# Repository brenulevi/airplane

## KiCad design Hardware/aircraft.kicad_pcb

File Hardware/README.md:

# FCU
- UART1: Comm with NU
- UART2: Logging Debug
- UART3: Extra UART (Radio Control)
- UART4: Extra UART (Camera)

- I2C1: Comm with NU
- I2C2: Peripherals (PWM Driver, EEPROM)

- TIM3: Actuators (CH1 Ailerons, CH2 Elevator, CH3 Rudder, CH4 Flaps)
- TIM1: Propulsions (CH1 ESC1, CH3 ESC3)

- SPI1: Peripherals (Flash)

- SWD: Coding/Debug

- SDIO: SD Card (1bit)

- GPIOA, GPIOC, GPIOE: Comm with NU (Output)
- GPIOB, GPIOD, GPIOF: Comm with NU (Input)

- DFU_USB_DP
- DFU_USB_DM
- DFU_USB_VBUS

# NU
- UART1: Comm with FCU
- UART2: Logging Debug
- UART3: Peripheral (GNSS)
- UART4: Extra UART

- I2C1: Comm with FCU
- I2C2: Peripherals (Temperature, Baro, EEPROM, MAG)
- I2C3: Extra I2C (Pitot Sensor)

- SPI1: Peripherals (Flash) + 1 GPIO CS
- SPI2: Peripherals (IMU) + 1 GPIO CS

- SWD: Coding/Debug

- GPIO_GPS_PSS
- GPIO_GPS_LNA_EN
- GPIO_GPS_NRST

- GPIOA, GPIOC, GPIOE: Comm with NU (Input)
- GPIOB, GPIOD, GPIOF: Comm with NU (Output)

- DFU_USB_DP
- DFU_USB_DM

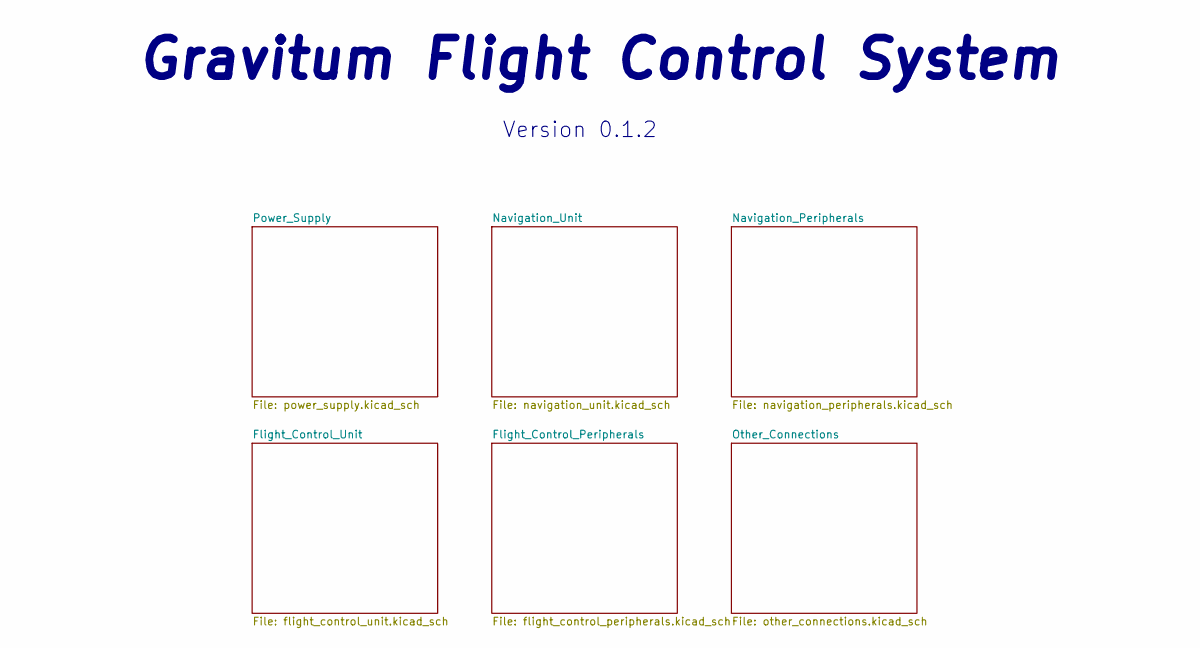
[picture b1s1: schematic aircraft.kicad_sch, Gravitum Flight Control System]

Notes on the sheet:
Gravitum Flight Control System
Version 0.1.2

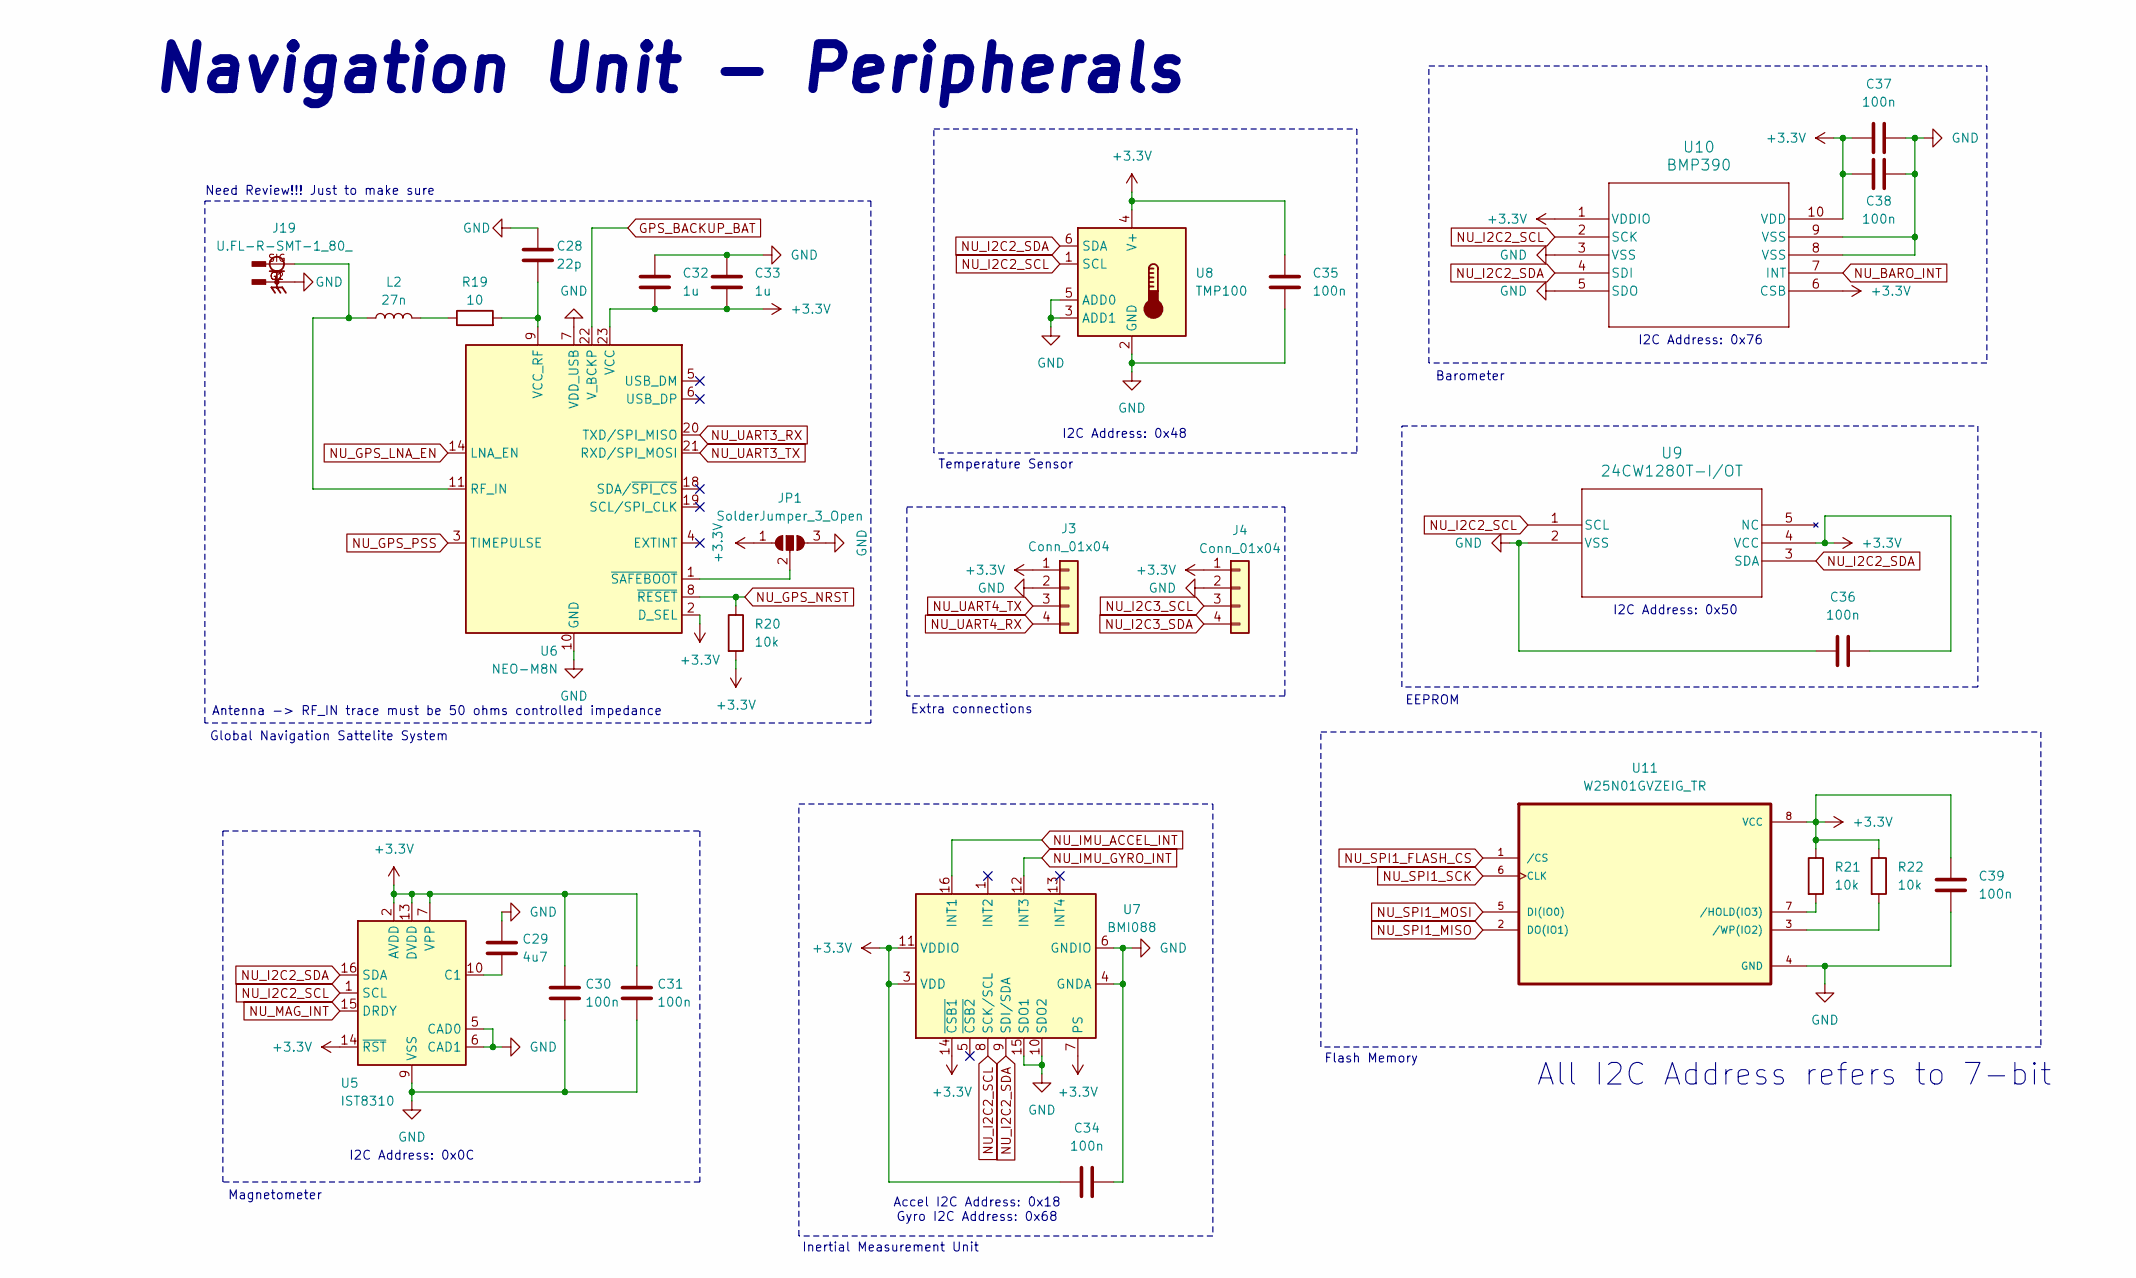
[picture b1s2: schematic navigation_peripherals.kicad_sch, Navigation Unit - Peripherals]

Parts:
C28: 22p; C_0603_1608Metric; MPN C0603C220J8GACTU
C29: 4u7; C_0805_2012Metric_Pad1.18x1.45mm_HandSolder; MPN CL21B475KPFNNNE
C30, C31, C34, C35, C36, C37, C38, C39: 100n; C_0603_1608Metric; MPN C0603C104K8RACTU
C32, C33: 1u; C_0603_1608Metric_Pad1.08x0.95mm_HandSolder; MPN CL10B105KP8NNNC
J3, J4: Conn_01x04; JST_PH_S4B-PH-K_1x04_P2.00mm_Horizontal; MPN S4B-PH-K-S
J19: U.FL-R-SMT-1_80_; HIROSE_U.FL-R-SMT-1_80_; PARTREV Jul.1.2022
JP1: SolderJumper_3_Open; SolderJumper-3_P1.3mm_Open_RoundedPad1.0x1.5mm_NumberLabels
L2: 27n; L_0603_1608Metric_Pad1.05x0.95mm_HandSolder; MPN B82496C3270J000
R19: 10; R_0603_1608Metric_Pad0.98x0.95mm_HandSolder; MPN RMCF0603FT10R0
R20, R21, R22: 10k; R_0603_1608Metric_Pad0.98x0.95mm_HandSolder; MPN RC0603FR-0710KL
U5: IST8310; LGA-16_3x3mm_P0.5mm; MPN IST8310
U6: NEO-M8N; XCVR_NEO-M8N-0; MPN NEO-M8N-0
U7: BMI088; Bosch_LGA-16_4.5x3mm_P0.5mm_LayoutBorder7x1y_ClockwisePinNu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; MPN BMI088
U8: TMP100; SOT-23-6; MPN TMP100NA-3K
U9: 24CW1280T-I/OT; SOT-23-5_2P9X1P6_MCH; MPN 24CW1280T-I/OT
U10: BMP390; 10LGA_2X2X0p75_BOS; MPN BMP390
U11: W25N01GVZEIG_TR; SON127P800X600X80-9N; MPN W25N01GVZEIG-TR

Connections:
+3.3V: C30.1, C31.1, C32.2, C33.2, C34.1, C35.2, C36.1, C37.2, C38.2, C39.1, J3.1, J4.1, JP1.1 (A), R20.2, R21.1, R22.1, U5.2 (AVDD), U5.7 (VPP), U5.13 (DVDD), U5.14 (~RST), U6.2 (D_SEL), U6.23 (VCC), U7.3 (VDD), U7.7 (PS), U7.11 (VDDIO), U7.14 (~CSB1), U8.4 (V+), U9.4 (VCC), U10.1 (VDDIO), U10.6 (CSB), U10.10 (VDD), U11.8 (VCC); also elsewhere on the board
GND: C28.1, C29.1, C30.2, C31.2, C32.1, C33.1, C34.2, C35.1, C36.2, C37.1, C38.1, C39.2, J3.2, J4.2, J19.G1, J19.G2, JP1.3 (B), U5.5 (CAD0), U5.6 (CAD1), U5.9 (VSS), U5.11 (VSS), U6.7 (VDD_USB), U6.10 (GND), U6.12 (GND), U6.13 (GND), U6.24 (GND), U7.2 (GNDA), U7.4 (GNDA), U7.6 (GNDIO), U7.10 (SDO2), U7.15 (SDO1), U8.2 (GND), U8.3 (ADD1), U8.5 (ADD0), U9.2 (VSS), U10.3 (VSS), U10.5 (SDO), U10.8 (VSS), U10.9 (VSS), U11.4 (GND); also elsewhere on the board
GPS_BACKUP_BAT: U6.22 (V_BCKP); also elsewhere on the board
NU_BARO_INT: U10.7 (INT); also elsewhere on the board
NU_GPS_LNA_EN: U6.14 (LNA_EN); also elsewhere on the board
NU_GPS_NRST: R20.1, U6.8 (~RESET); also elsewhere on the board
NU_GPS_PSS: U6.3 (TIMEPULSE); also elsewhere on the board
NU_I2C2_SCL: U5.1 (SCL), U7.8 (SCK/SCL), U8.1 (SCL), U9.1 (SCL), U10.2 (SCK); also elsewhere on the board
NU_I2C2_SDA: U5.16 (SDA), U7.9 (SDI/SDA), U8.6 (SDA), U9.3 (SDA), U10.4 (SDI); also elsewhere on the board
NU_I2C3_SCL: J4.3; also elsewhere on the board
NU_I2C3_SDA: J4.4; also elsewhere on the board
NU_IMU_ACCEL_INT: U7.16 (INT1); also elsewhere on the board
NU_IMU_GYRO_INT: U7.12 (INT3); also elsewhere on the board
NU_MAG_INT: U5.15 (DRDY); also elsewhere on the board
NU_SPI1_FLASH_CS: U11.1 (/CS); also elsewhere on the board
NU_SPI1_MISO: U11.2 (DO(IO1)); also elsewhere on the board
NU_SPI1_MOSI: U11.5 (DI(IO0)); also elsewhere on the board
NU_SPI1_SCK: U11.6 (CLK); also elsewhere on the board
NU_UART3_RX: U6.20 (TXD/SPI_MISO); also elsewhere on the board
NU_UART3_TX: U6.21 (RXD/SPI_MOSI); also elsewhere on the board
NU_UART4_RX: J3.4; also elsewhere on the board
NU_UART4_TX: J3.3; also elsewhere on the board
unnamed: JP1.2 (C), U6.1 (~SAFEBOOT)
unnamed: L2.2, R19.1
unnamed: C29.2, U5.10 (C1)
unnamed: J19.SIG, L2.1, U6.11 (RF_IN)
unnamed: C28.2, R19.2, U6.9 (VCC_RF)
unnamed: R21.2, U11.7 (/HOLD(IO3))
unnamed: R22.2, U11.3 (/WP(IO2))

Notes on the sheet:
Magnetometer
Navigation Unit - Peripherals
I2C Address: 0x48
Flash Memory
I2C Address: 0x76
Barometer
Temperature Sensor
Accel I2C Address: 0x18 Gyro I2C Address: 0x68
EEPROM
Need Review!!! Just to make sure
Global Navigation Sattelite System
Inertial Measurement Unit
All I2C Address refers to 7-bit
Antenna -> RF_IN trace must be 50 ohms controlled impedance
I2C Address: 0x0C
I2C Address: 0x50
Extra connections

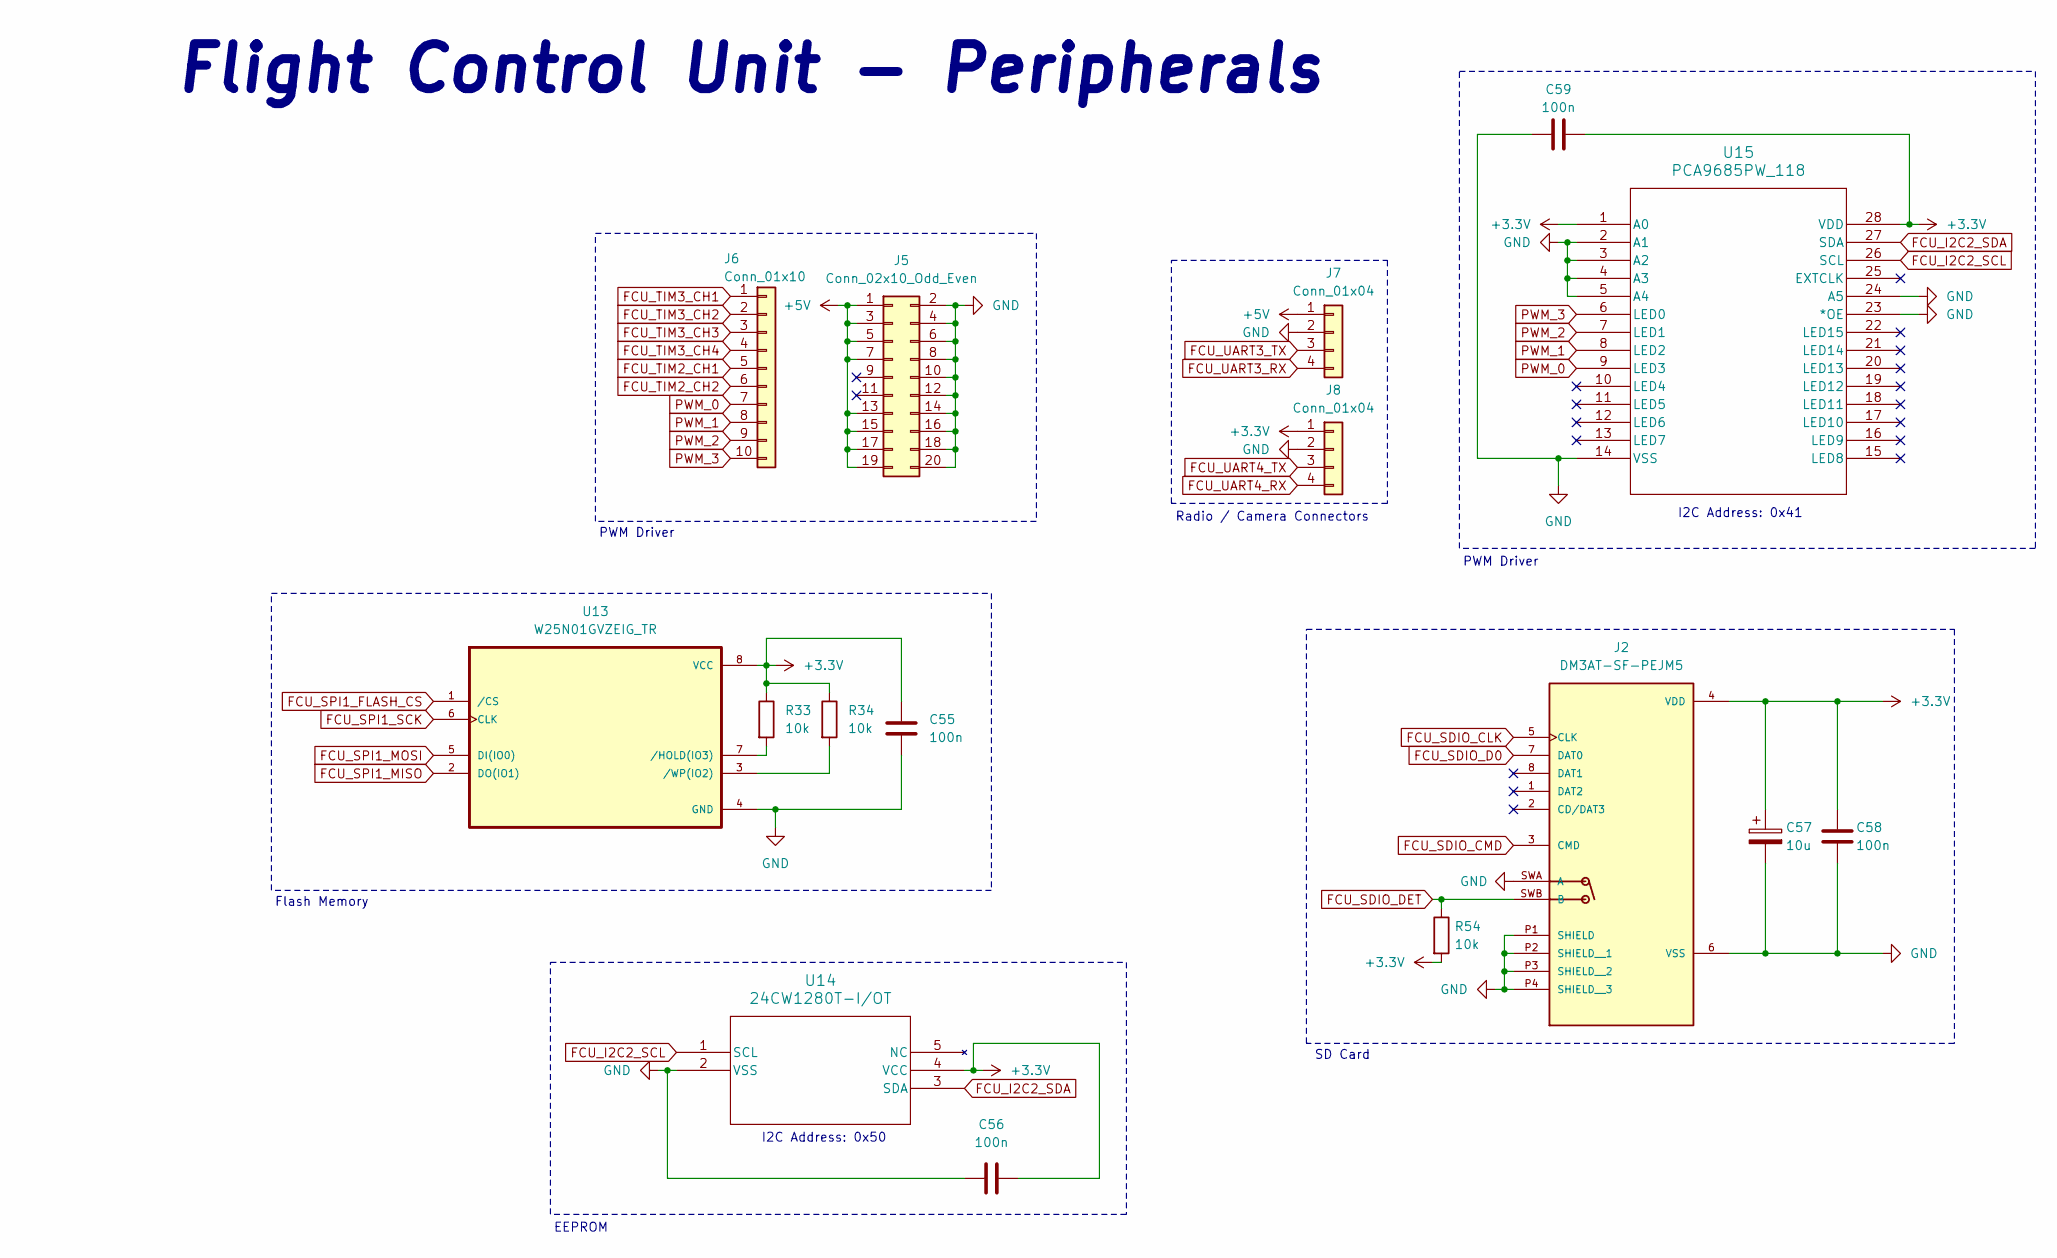
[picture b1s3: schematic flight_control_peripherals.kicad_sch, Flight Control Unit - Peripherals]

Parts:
C55, C56, C58, C59: 100n; C_0402_1005Metric; MPN C0603C104K8RACTU
C57: 10u; C_0603_1608Metric; MPN TAJA106K010TNJ
J2: DM3AT-SF-PEJM5; HRS_DM3AT-SF-PEJM5; PARTREV 20200913
J5: Conn_02x10_Odd_Even; PinHeader_2x10_P2.54mm_Vertical
J6: Conn_01x10; PinHeader_1x10_P2.54mm_Vertical
J7, J8: Conn_01x04; JST_PH_S4B-PH-K_1x04_P2.00mm_Horizontal; MPN S4B-PH-K-S
R33, R34, R54: 10k; R_0402_1005Metric; MPN RC0603FR-0710KL
U13: W25N01GVZEIG_TR; SON127P800X600X80-9N; MPN W25N01GVZEIG-TR
U14: 24CW1280T-I/OT; SOT-23-5_2P9X1P6_MCH; MPN 24CW1280T-I/OT
U15: PCA9685PW_118; TSSOP28_SOT361-1_NXP; MPN PCA9685PW,118

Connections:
+3.3V: C55.1, C56.1, C57.1, C58.1, C59.1, J2.4 (VDD), J8.1, R33.1, R34.1, R54.2, U13.8 (VCC), U14.4 (VCC), U15.1 (A0), U15.28 (VDD); also elsewhere on the board
+5V: J5.1, J5.3, J5.5, J5.7, J5.13, J5.15, J5.17, J5.19, J7.1; also elsewhere on the board
FCU_I2C2_SCL: U14.1 (SCL), U15.26 (SCL); also elsewhere on the board
FCU_I2C2_SDA: U14.3 (SDA), U15.27 (SDA); also elsewhere on the board
FCU_SDIO_CLK: J2.5 (CLK); also elsewhere on the board
FCU_SDIO_CMD: J2.3 (CMD); also elsewhere on the board
FCU_SDIO_D0: J2.7 (DAT0); also elsewhere on the board
FCU_SDIO_DET: J2.SWB (B), R54.1; also elsewhere on the board
FCU_SPI1_FLASH_CS: U13.1 (/CS); also elsewhere on the board
FCU_SPI1_MISO: U13.2 (DO(IO1)); also elsewhere on the board
FCU_SPI1_MOSI: U13.5 (DI(IO0)); also elsewhere on the board
FCU_SPI1_SCK: U13.6 (CLK); also elsewhere on the board
FCU_TIM2_CH1: J6.5; also elsewhere on the board
FCU_TIM2_CH2: J6.6; also elsewhere on the board
FCU_TIM3_CH1: J6.1; also elsewhere on the board
FCU_TIM3_CH2: J6.2; also elsewhere on the board
FCU_TIM3_CH3: J6.3; also elsewhere on the board
FCU_TIM3_CH4: J6.4; also elsewhere on the board
FCU_UART3_RX: J7.4; also elsewhere on the board
FCU_UART3_TX: J7.3; also elsewhere on the board
FCU_UART4_RX: J8.4; also elsewhere on the board
FCU_UART4_TX: J8.3; also elsewhere on the board
GND: C55.2, C56.2, C57.2, C58.2, C59.2, J2.6 (VSS), J2.P1 (SHIELD), J2.P2 (SHIELD__1), J2.P3 (SHIELD__2), J2.P4 (SHIELD__3), J2.SWA (A), J5.2, J5.4, J5.6, J5.8, J5.10, J5.12, J5.14, J5.16, J5.18, J5.20, J7.2, J8.2, U13.4 (GND), U14.2 (VSS), U15.2 (A1), U15.3 (A2), U15.4 (A3), U15.5 (A4), U15.14 (VSS), U15.23 (*OE), U15.24 (A5); also elsewhere on the board
unnamed: R33.2, U13.7 (/HOLD(IO3))
unnamed: R34.2, U13.3 (/WP(IO2))
PWM_0: J6.7, U15.9 (LED3)
PWM_1: J6.8, U15.8 (LED2)
PWM_2: J6.9, U15.7 (LED1)
PWM_3: J6.10, U15.6 (LED0)

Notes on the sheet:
I2C Address: 0x50
I2C Address: 0x41
Radio / Camera Connectors
SD Card
PWM Driver
Flash Memory
Flight Control Unit - Peripherals
EEPROM

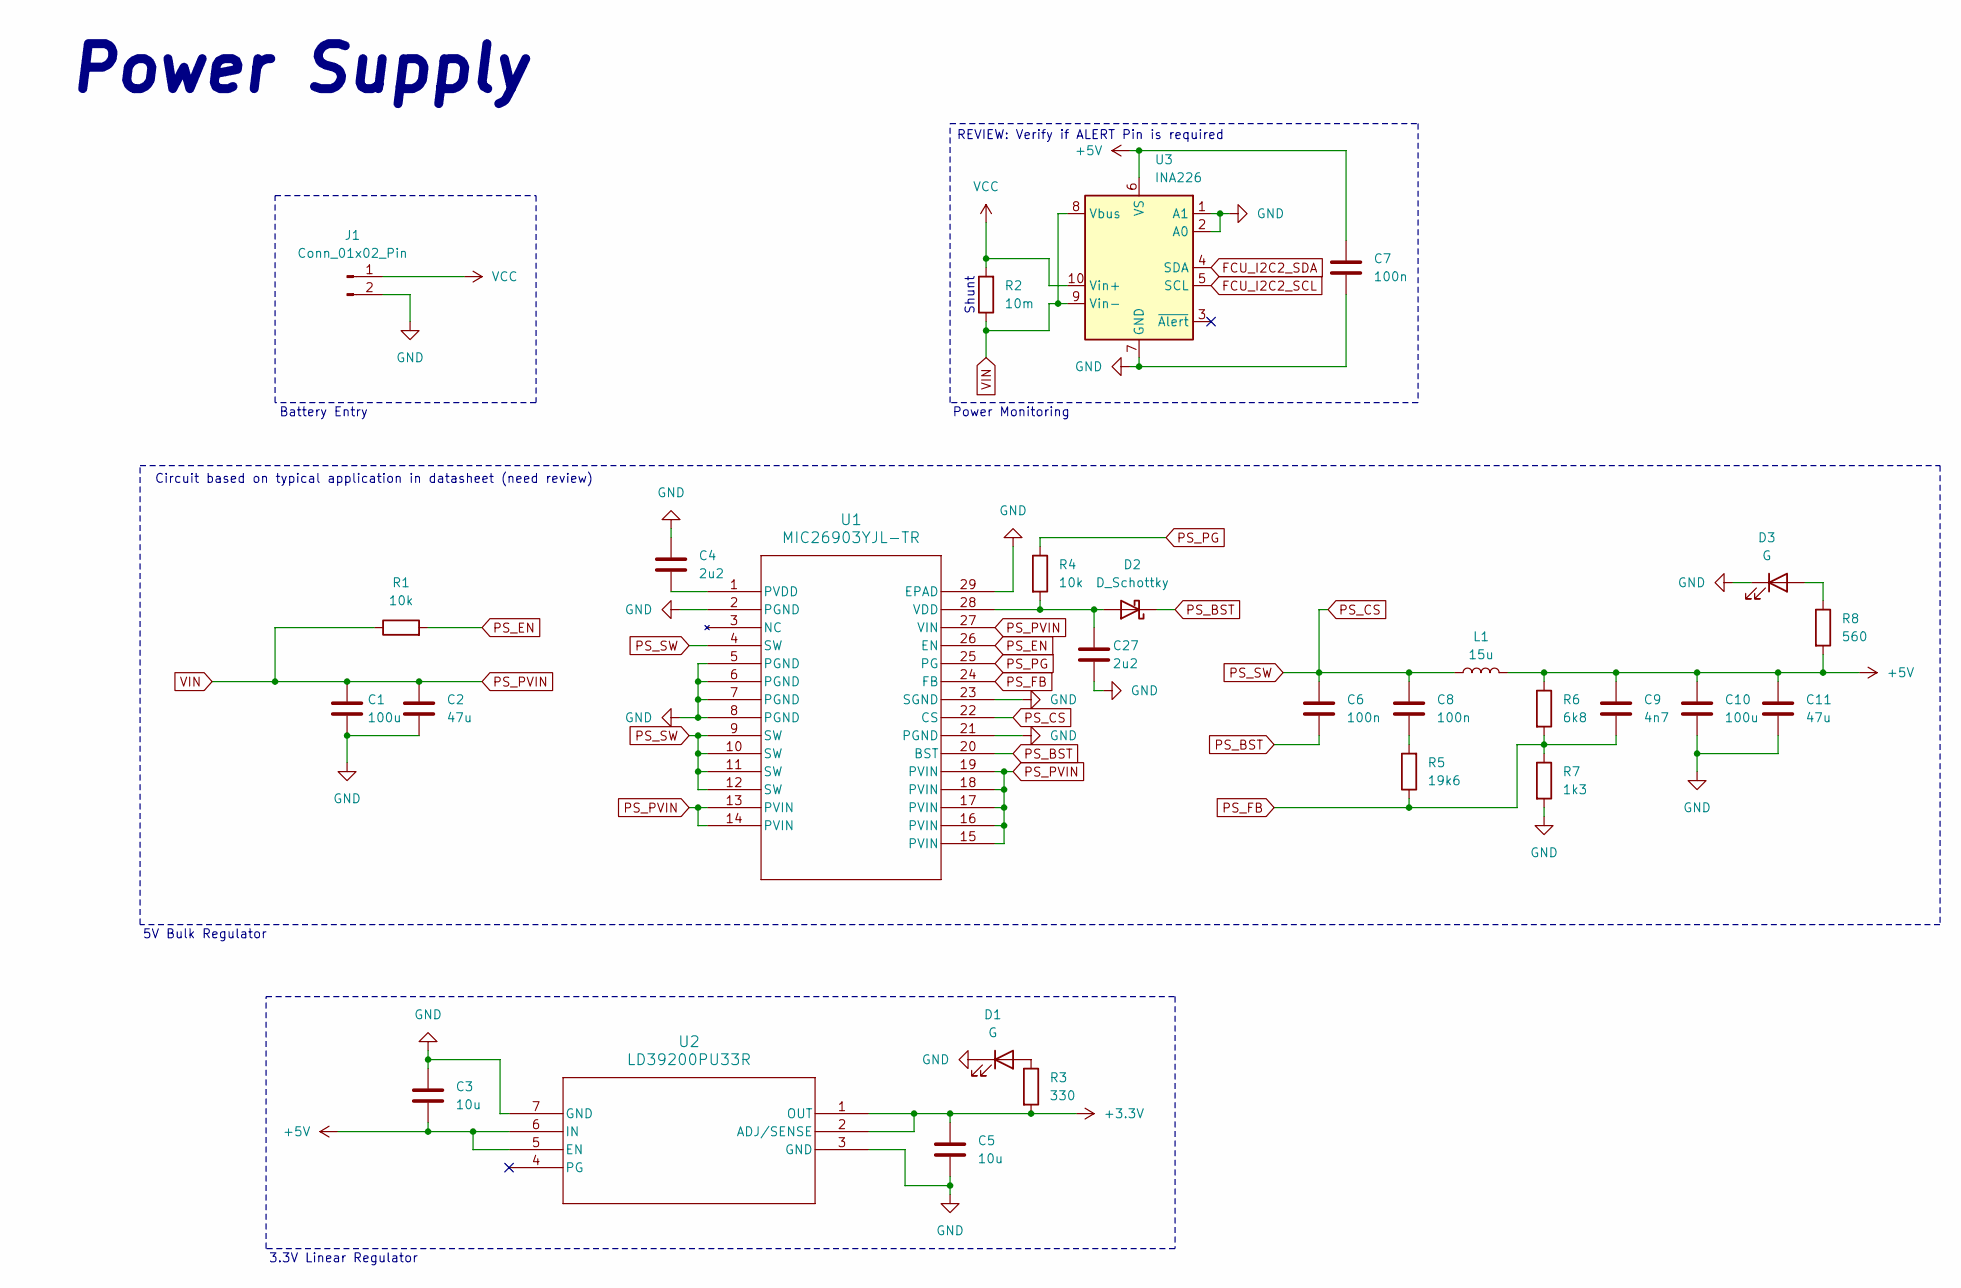
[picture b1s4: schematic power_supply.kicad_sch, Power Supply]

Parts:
C1, C10: 100u; C_Elec_6.3x7.7; MPN A768EB107M1ELAS036
C2, C11: 47u; C_1206_3216Metric_Pad1.33x1.80mm_HandSolder; MPN C3216X5R1E476M160AC
C3, C5: 10u; C_0805_2012Metric_Pad1.18x1.45mm_HandSolder; MPN CL21B106KPQNNNE
C4, C27: 2u2; C_0805_2012Metric_Pad1.18x1.45mm_HandSolder; MPN 08053C225KAT2A
C6, C7, C8: 100n; C_0603_1608Metric_Pad1.08x0.95mm_HandSolder; MPN C0603C104K3RACTU
C9: 4n7; C_0603_1608Metric_Pad1.08x0.95mm_HandSolder; MPN C0603C472F3GACTU
D1, D3: G; LED_0603_1608Metric_Pad1.05x0.95mm_HandSolder; MPN LTST-S270KGKT
D2: D_Schottky; D_SOD-323_HandSoldering; MPN SD103AWS
J1: Conn_01x02_Pin; AMASS_XT60-M_1x02_P7.20mm_Vertical; MPN 11864
L1: 15u; IND_PA4343_FOOTPRINT2_PUL; MPN PA4343-103ANLT
R1, R4: 10k; R_0603_1608Metric_Pad0.98x0.95mm_HandSolder; MPN RC0603FR-0710KL
R2: 10m; R_2512_6332Metric_Pad1.40x3.35mm_HandSolder; MPN CRF2512-FZ-R010ELF
R3: 330; R_0603_1608Metric_Pad0.98x0.95mm_HandSolder; MPN RC0603JR-07330RL
R5: 19k6; R_0603_1608Metric_Pad0.98x0.95mm_HandSolder; MPN CRCW060319K6FKEAC
R6: 6k8; R_0603_1608Metric_Pad0.98x0.95mm_HandSolder; MPN RC0603JR-076K8L
R7: 1k3; R_0603_1608Metric_Pad0.98x0.95mm_HandSolder; MPN RC0603JR-071K3L
R8: 560; R_0603_1608Metric_Pad0.98x0.95mm_HandSolder; MPN RMCF0603FT560R
U1: MIC26903YJL-TR; MLF28_5X6_MCH; MPN MIC26903YJL-TR
U2: LD39200PU33R; SON_DFN6_3X3_STM; MPN LD39200PU33R
U3: INA226; DGS10; MPN INA226AIDGST

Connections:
+3.3V: C5.1, R3.2, U2.1 (OUT), U2.2 (ADJ/SENSE); also elsewhere on the board
+5V: C3.2, C7.1, C9.1, C10.1, C11.1, L1.2, R6.1, R8.2, U2.5 (EN), U2.6 (IN), U3.6 (VS); also elsewhere on the board
FCU_I2C2_SCL: U3.5 (SCL); also elsewhere on the board
FCU_I2C2_SDA: U3.4 (SDA); also elsewhere on the board
GND: C1.2, C2.2, C3.1, C4.1, C5.2, C7.2, C10.2, C11.2, C27.2, D1.1 (K), D3.1 (K), J1.2, R7.2, U1.2 (PGND), U1.5 (PGND), U1.6 (PGND), U1.7 (PGND), U1.8 (PGND), U1.21 (PGND), U1.23 (SGND), U1.29 (EPAD), U2.3 (GND), U2.7 (GND), U3.1 (A1), U3.2 (A0), U3.7 (GND); also elsewhere on the board
unnamed: C8.2, R5.2
unnamed: D1.2 (A), R3.1
unnamed: C27.1, D2.2 (A), R4.2, U1.28 (VDD)
unnamed: D3.2 (A), R8.1
unnamed: C4.2, U1.1 (PVDD)
PS_BST: C6.2, D2.1 (K), U1.20 (BST)
PS_CS: C6.1, C8.1, L1.1, U1.4 (SW), U1.9 (SW), U1.10 (SW), U1.11 (SW), U1.12 (SW), U1.22 (CS)
PS_EN: R1.2, U1.26 (EN)
PS_FB: C9.2, R5.1, R6.2, R7.1, U1.24 (FB)
PS_PG: R4.1, U1.25 (PG)
PS_PVIN: C1.1, C2.1, R1.1, R2.1, U1.13 (PVIN), U1.14 (PVIN), U1.15 (PVIN), U1.16 (PVIN), U1.17 (PVIN), U1.18 (PVIN), U1.19 (PVIN), U1.27 (VIN), U3.8 (Vbus), U3.9 (Vin-); also elsewhere on the board
VIN+: J1.1, R2.2, U3.10 (Vin+); also elsewhere on the board

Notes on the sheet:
Power Supply
Shunt
5V Bulk Regulator
REVIEW: Verify if ALERT Pin is required
Circuit based on typical application in datasheet (need review)
Battery Entry
3.3V Linear Regulator
Power Monitoring

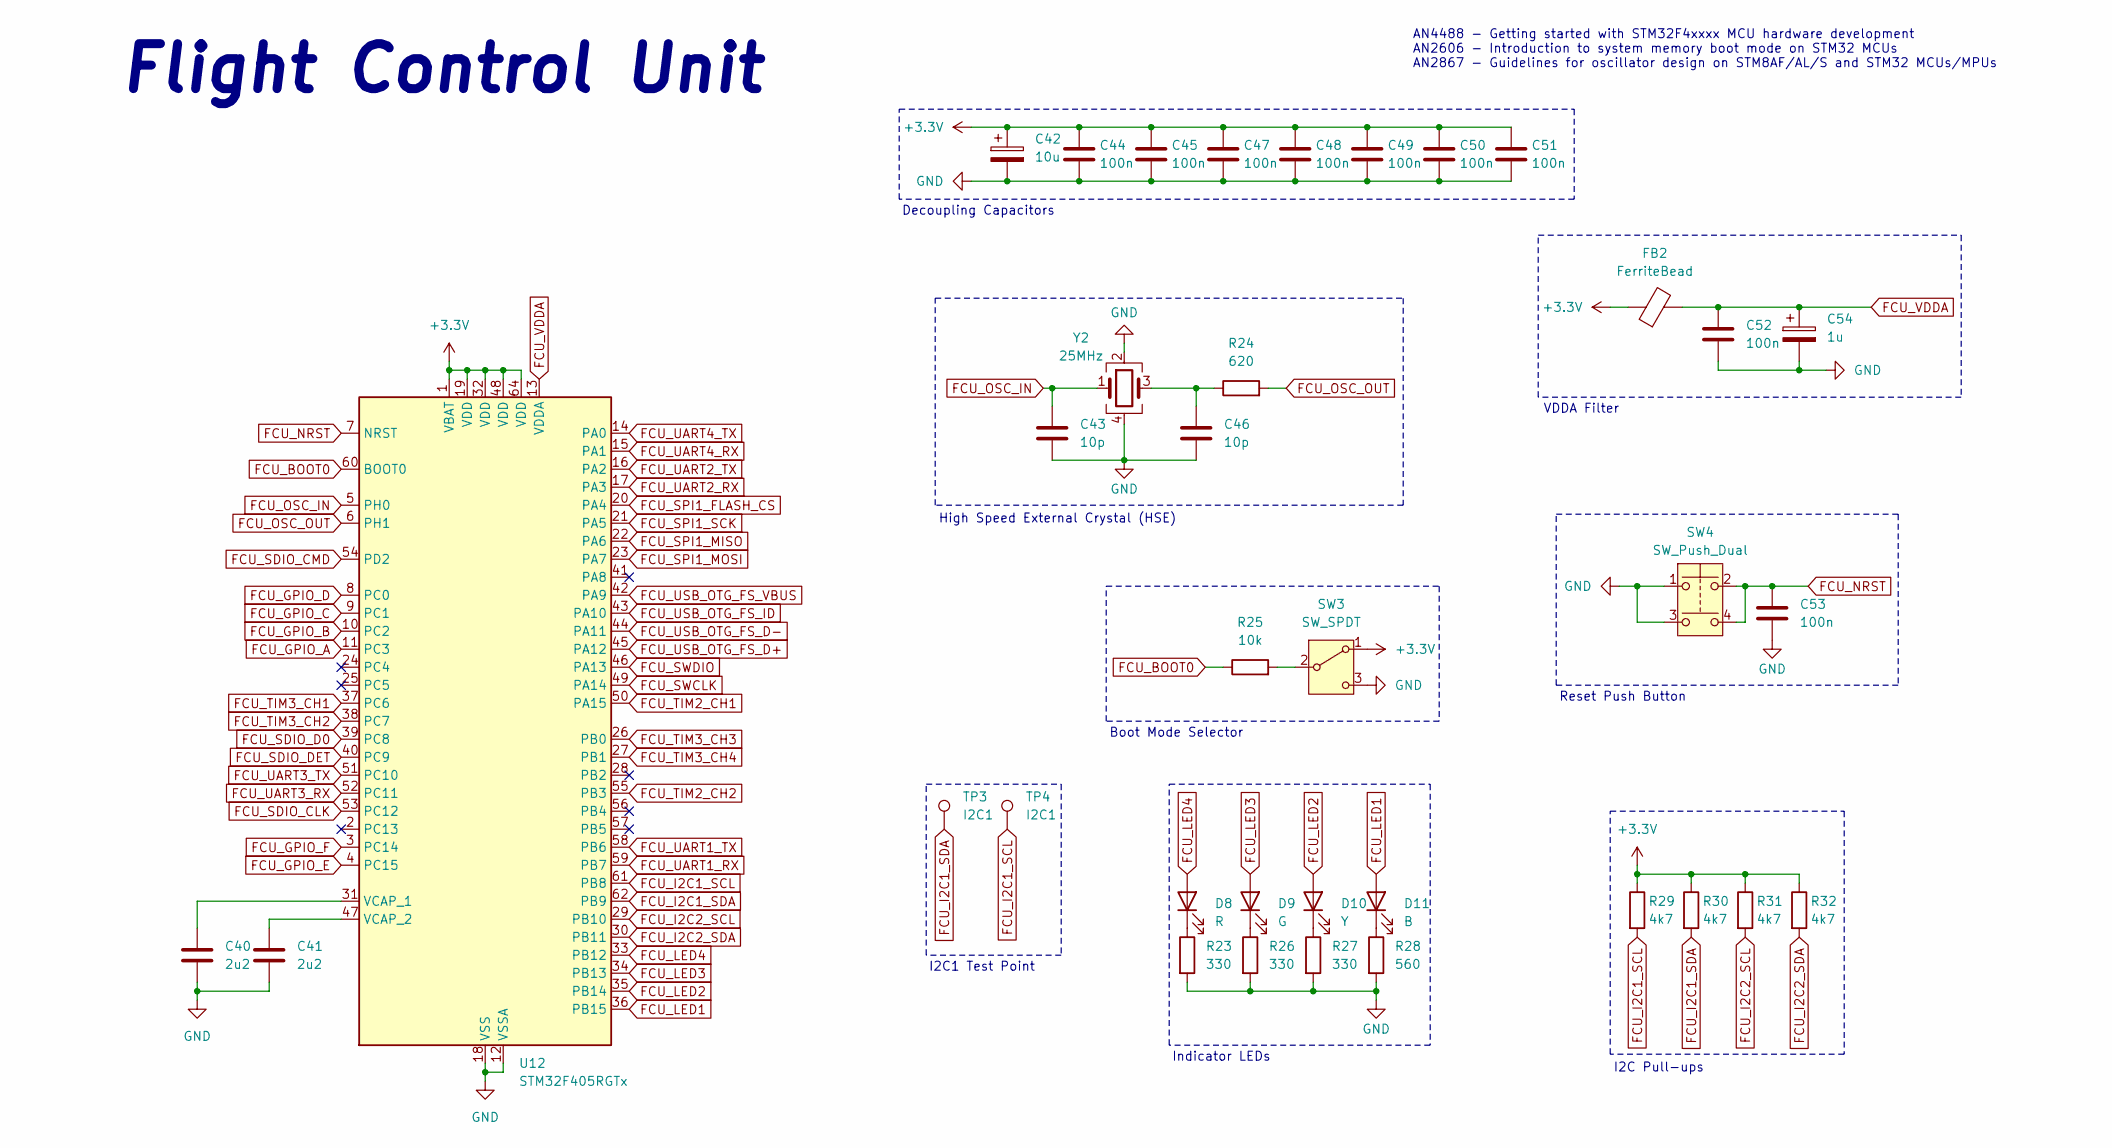
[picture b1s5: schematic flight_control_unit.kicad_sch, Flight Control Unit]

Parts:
C40, C41: 2u2; C_0402_1005Metric; MPN CL10B225KP8NNNC
C42: 10u; C_0603_1608Metric; MPN TAJA106K010TNJ
C43, C46: 10p; C_0402_1005Metric; MPN 885012005007
C44, C45, C47, C48, C49, C50, C51, C52: 100n; C_0402_1005Metric; MPN CL05B104KP5NNNC
C53: 100n; C_0402_1005Metric; MPN C0603C104K8RACTU
C54: 1u; CP_EIA-1608-08_AVX-J; MPN T491A105K010AT
D8: R; LED_0402_1005Metric; MPN LTST-C171KRKT
D9: G; LED_0402_1005Metric; MPN LTST-C170GKT
D10: Y; LED_0402_1005Metric; MPN LTST-C171YKT
D11: B; LED_0402_1005Metric; MPN LTST-C171TBKT
FB2: FerriteBead; L_0402_1005Metric; MPN HZ0805E601R-10
R23, R26, R27: 330; R_0402_1005Metric; MPN RC0603JR-07330RL
R24: 620; R_0402_1005Metric; MPN RC0603FR-07620RL
R25: 10k; R_0402_1005Metric; MPN RC0603FR-0710KL
R28: 560; R_0402_1005Metric; MPN RMCF0603FT560R
R29, R30, R31, R32: 4k7; R_0402_1005Metric; MPN ERJ-3EKF4701V
SW3: SW_SPDT; SW_SPDT_PCM12; MPN PCM12SMTR
SW4: SW_Push_Dual; SW4_PTS815 SJM 250 SMTR LFS_CNK; MPN PTS815SJM250SMTRLFS
TP3, TP4: I2C1; TestPoint_Pad_D1.0mm
U12: STM32F405RGTx; LQFP-64_10x10mm_P0.5mm; MPN STM32F405RGT6
Y2: 25MHz; Crystal_SMD_Abracon_ABM8G-4Pin_3.2x2.5mm; MPN ABM8G-25.000MHZ-B4Y-T3

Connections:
+3.3V: C42.1, C44.1, C45.1, C47.1, C48.1, C49.1, C50.1, C51.1, FB2.1, R29.1, R30.1, R31.1, R32.1, SW3.1 (A), U12.1 (VBAT), U12.19 (VDD), U12.32 (VDD), U12.48 (VDD), U12.64 (VDD); also elsewhere on the board
FCU_BOOT0: R25.1, U12.60 (BOOT0)
FCU_GPIO_A: U12.11 (PC3); also elsewhere on the board
FCU_GPIO_B: U12.10 (PC2); also elsewhere on the board
FCU_GPIO_C: U12.9 (PC1); also elsewhere on the board
FCU_GPIO_D: U12.8 (PC0); also elsewhere on the board
FCU_GPIO_E: U12.4 (PC15); also elsewhere on the board
FCU_GPIO_F: U12.3 (PC14); also elsewhere on the board
FCU_I2C1_SCL: R29.2, TP4.1, U12.61 (PB8); also elsewhere on the board
FCU_I2C1_SDA: R30.2, TP3.1, U12.62 (PB9); also elsewhere on the board
FCU_I2C2_SCL: R31.2, U12.29 (PB10); also elsewhere on the board
FCU_I2C2_SDA: R32.2, U12.30 (PB11); also elsewhere on the board
FCU_LED1: D11.2 (A), U12.36 (PB15)
FCU_LED2: D10.2 (A), U12.35 (PB14)
FCU_LED3: D9.2 (A), U12.34 (PB13)
FCU_LED4: D8.2 (A), U12.33 (PB12)
FCU_NRST: C53.1, SW4.2, SW4.4, U12.7 (NRST); also elsewhere on the board
FCU_OSC_IN: C43.1, U12.5 (PH0), Y2.1
FCU_OSC_OUT: R24.2, U12.6 (PH1)
FCU_SDIO_CLK: U12.53 (PC12); also elsewhere on the board
FCU_SDIO_CMD: U12.54 (PD2); also elsewhere on the board
FCU_SDIO_D0: U12.39 (PC8); also elsewhere on the board
FCU_SDIO_DET: U12.40 (PC9); also elsewhere on the board
FCU_SPI1_FLASH_CS: U12.20 (PA4); also elsewhere on the board
FCU_SPI1_MISO: U12.22 (PA6); also elsewhere on the board
FCU_SPI1_MOSI: U12.23 (PA7); also elsewhere on the board
FCU_SPI1_SCK: U12.21 (PA5); also elsewhere on the board
FCU_SWCLK: U12.49 (PA14); also elsewhere on the board
FCU_SWDIO: U12.46 (PA13); also elsewhere on the board
FCU_TIM2_CH1: U12.50 (PA15); also elsewhere on the board
FCU_TIM2_CH2: U12.55 (PB3); also elsewhere on the board
FCU_TIM3_CH1: U12.37 (PC6); also elsewhere on the board
FCU_TIM3_CH2: U12.38 (PC7); also elsewhere on the board
FCU_TIM3_CH3: U12.26 (PB0); also elsewhere on the board
FCU_TIM3_CH4: U12.27 (PB1); also elsewhere on the board
FCU_UART1_RX: U12.59 (PB7); also elsewhere on the board
FCU_UART1_TX: U12.58 (PB6); also elsewhere on the board
FCU_UART2_RX: U12.17 (PA3); also elsewhere on the board
FCU_UART2_TX: U12.16 (PA2); also elsewhere on the board
FCU_UART3_RX: U12.52 (PC11); also elsewhere on the board
FCU_UART3_TX: U12.51 (PC10); also elsewhere on the board
FCU_UART4_RX: U12.15 (PA1); also elsewhere on the board
FCU_UART4_TX: U12.14 (PA0); also elsewhere on the board
FCU_USB_OTG_FS_D+: U12.45 (PA12); also elsewhere on the board
FCU_USB_OTG_FS_D-: U12.44 (PA11); also elsewhere on the board
FCU_USB_OTG_FS_ID: U12.43 (PA10); also elsewhere on the board
FCU_USB_OTG_FS_VBUS: U12.42 (PA9); also elsewhere on the board
FCU_VDDA: C52.1, C54.1, FB2.2, U12.13 (VDDA)
GND: C40.2, C41.2, C42.2, C43.2, C44.2, C45.2, C46.2, C47.2, C48.2, C49.2, C50.2, C51.2, C52.2, C53.2, C54.2, R23.2, R26.2, R27.2, R28.2, SW3.3 (C), SW4.1, SW4.3, U12.12 (VSSA), U12.18 (VSS), U12.63 (VSS), Y2.2, Y2.4; also elsewhere on the board
unnamed: C46.1, R24.1, Y2.3
unnamed: D8.1 (K), R23.1
unnamed: D9.1 (K), R26.1
unnamed: D10.1 (K), R27.1
unnamed: D11.1 (K), R28.1
unnamed: R25.2, SW3.2 (B)
unnamed: C40.1, U12.31 (VCAP_1)
unnamed: C41.1, U12.47 (VCAP_2)

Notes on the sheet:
Reset Push Button
VDDA Filter
Decoupling Capacitors
I2C Pull-ups
Flight Control Unit
AN4488 - Getting started with STM32F4xxxx MCU hardware development AN2606 - Introduction to system memory boot mode on STM32 MCUs AN2867 - Guidelines for oscillator design on STM8AF/AL/S and STM32 MCUs/MPUs
Indicator LEDs
Boot Mode Selector
High Speed External Crystal (HSE)
I2C1 Test Point
